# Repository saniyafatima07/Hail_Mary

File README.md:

# Low Cost Precision Guidance and Smart Electronic Fuze System for a 155 mm Artillery Shell

A low cost Precision Guidance System Kit prototype designed as a modular electronics package that can be integrated with an existing 155 mm artillery shell form factor. The system combines inertial sensing, GNSS positioning, environmental monitoring, BLDC based actuation and multi mode event detection to demonstrate the architecture of a retrofit guidance and electronic fuze platform.

## Demo Video

https://github.com/user-attachments/assets/ea4bcfed-2732-404f-be3d-91d5685b1a28

## Overview

The **Low Cost Precision Guidance and Smart Electronic Fuze System** is focused on integrating embedded sensing, navigation, actuation and a multi-mode electronic fuze architecture.

The system is designed around a modular embedded platform that combines inertial sensing, GNSS positioning, atmospheric monitoring, power telemetry, proximity detection, impact/event sensing, and **BLDC based actuation**.

The current V1 prototype uses an **ESP32** as the primary embedded controller and integrates:

- **MPU6050**:  6 axis inertial measurement
- **NEO-6M**:  GNSS positioning
- **BMP280**:  Barometric pressure and temperature
- **INA219**:  Voltage and current monitoring
- **IR Proximity Sensor**:  Proximity detection
- **SW-240**:  Impact/vibration event detection
- **BLDC Motor**:  Actuation mechanism for the prototype guidance subsystem

The system supports a **Multi-Mode Smart Fuze architecture** consisting of:

- **Proximity Mode**
- **Time Mode**
- **Impact Mode**

The V1 platform is intended primarily for **Testing, sensor integration, firmware development, simulation, telemetry, and proof of concept validation**.

---

## Project Objectives

The project aims to develop a compact and modular embedded platform capable of supporting:

1. Inertial sensing
2. GNSS positioning
3. Environmental sensing
4. Power monitoring
5. Proximity detection
6. Impact/event detection
7. BLDC-based actuation
8. Multi mode fuze state management
9. Sensor fusion
10. Real time telemetry

---

## Prototype Hardware

| Component | Function | Interface |
|---|---|---|
| **ESP32** | Main microcontroller | — |
| **MPU6050** | 6 axis inertial measurement | I2C |
| **NEO-6M** | GNSS/GPS positioning | UART |
| **BMP280** | Barometric pressure and temperature | I2C |
| **INA219** | Voltage and current monitoring | I2C |
| **IR Sensor** | Proximity detection | GPIO |
| **SW-240** | Impact/vibration detection | GPIO |
| **BLDC Motor** | Prototype actuation | Motor Driver / PWM |

---

## Simulation Stack                                                                                                                                                                      
                                                                                                                                                                                            
   The simulation is a three-layer chain, from pure physics to the real embedded                                                                                                            
   controller. Each layer validates the one above it, and every equation is                                                                                                                 
   traceable to published exterior-ballistics literature (McCoy *Modern Exterior                                                                                                            
   Ballistics*, Raza & Wang 2022, Cheng 2019, Chusilp 2012, Glebocki 2022).                                                                                                                 
                                                                                                                                                                                            
   ```text                                                                                                                                                                                  
   +---------------------------------------------------------------+                                                                                                                        
   |  LAYER 1 — 3-DOF FLIGHT PHYSICS (truth model)                 |                                                                                                                        
   |  point-mass trajectory: ISA atmosphere, Mach-dependent Cd,    |                                                                                                                        
   |  altitude wind profile, spin decay, Magnus, yaw of repose     |                                                                                                                        
   +------------------------------+--------------------------------+                                                                                                                        
                                  |                                                                                                                                                         
           +----------------------+----------------------+                                                                                                                                  
           v                                             v                                                                                                                                  
   +---------------------------+   +--------------------------------------+                                                                                                                 
   | LAYER 2 — HARDWARE-IN-    |   | LAYER 3 — ONBOARD-GNC SIL            |                                                                                                                 
   | THE-LOOP (HIL)            |   | (guidance_ordnance.m)                |                                                                                                                 
   | (guided_sensor.m)         |   | firmware_true.ino's exact math       |                                                                                                                 
   | PC flies the physics,     |   | (estimator + impact predictor +      |                                                                                                                 
   | REAL ESP32 streams real   |   | guidance law) flies the round using  |                                                                                                                 
   | sensor telemetry over     |   | ONLY noisy simulated baro/GPS at     |                                                                                                                 
   | UART; PC streams back     |   | board rates. Validates the onboard   |                                                                                                                 
   | canard commands in        |   | algorithm BEFORE flashing.           |                                                                                                                 
   | real time (1x - 4x).      |   |                                      |                                                                                                                 
   +---------------------------+   +--------------------------------------+                                                                                                                 
 ```

The GNC Math (implemented in firmware + validated in sim)                                                                                                                                  
                                                                                                                                                                                            
 - Firing solution (Chusilp 2012): bisection on gun elevation, secant                                                                                                                       
   iteration on azimuth for wind-drift cancellation.                                                                                                                                        
 - State estimation on board: baro altitude via hypsometric equation;                                                                                                                       
   vertical speed from a first-order complementary filter                                                                                                                                   
   vz ← 0.8·vz + 0.2·(Δh/Δt) at 10 Hz; GPS velocity smoothing at 1 Hz.                                                                                                                      
 - Impact Point Prediction (IPP) (McCoy; Raza & Wang 2022 use MPLT — we use                                                                                                                 
   the analytic point-mass equivalent an ESP32 can run in µs):                                                                                                                              
   closed-form time-to-impact τ = (vz + √(vz² + 2gz))/g, then drag-decay                                                                                                                    
   ballistic coast x_imp = x + vx·(1 − e^(−kd·τ))/kd.                                                                                                                                       
 - Guidance law: saturated proportional correction                                                                                                                                          
   δ = sat(Kp·(x_tgt − x_imp), ±15°), active post-apogee, 1 Hz.                                                                                                                             
 - Single-channel roll-orientation steering (Cheng 2019, Raza & Wang 2022):                                                                                                                 
   fixed-cant canards on the fuze cone; force orientation is the control                                                                                                                    
   variable, matching the dual-spin PGK architecture (M1156, Burke & Pergolizzi 2008).

## System Architecture

```text
                         +-------------------------+
                         |          ESP32          |
                         |    Main Controller      |
                         +------------+------------+
                                      |
              +-----------------------+-----------------------+
              |                       |                       |
              v                       v                       v
        +-----------+           +-----------+           +-----------+
        |    I2C    |           |   UART    |           |   GPIO    |
        |    Bus    |           | Interface |           |  Inputs   |
        +-----+-----+           +-----+-----+           +-----+-----+
              |                       |                       |
       +------+------+------+          |                 +----+----+
       |      |      |      |          |                 |         |
       v      v      v      |          v                 v         v
    MPU6050 BMP280 INA219  |       NEO-6M           IR Sensor   SW-240
       |      |      |      |          |             Proximity   Impact
       +------+------+------+          |                 |         |
              |                         |                 |         |
              v                         v                 |         |
       Motion / Environment       GNSS Position           |         |
              |                         |                 |         |
              +-------------+-----------+-----------------+---------+
                            |
                            v
                  +----------------------+
                  |   Sensor Processing  |
                  |   & State Estimation |
                  +----------+-----------+
                             |
                +------------+------------+
                |                         |
                v                         v
        +---------------+         +---------------+
        | Guidance &    |         | Smart Fuze    |
        | Navigation    |         | Manager       |
        +-------+-------+         +-------+-------+
                |                         |
                v                         |
        +---------------+                 |
        | Actuation     |                 |
        | Controller    |                 |
        +-------+-------+                 |
                |                         |
                v                         |
        +---------------+                 |
        | BLDC Motor &  |                 |
        | Motor Driver  |                 |
        +---------------+                 |
                                          |
                              +-----------+-----------+
                              |           |           |
                              v           v           v
                         +---------+ +---------+ +---------+
                         |Proximity| |  Time   | | Impact  |
                         |  Mode   | |  Mode   | |  Mode   |
                         +---------+ +---------+ +---------+
                              |           |           |
                              +-----------+-----------+
                                          |
                                          v
                                +----------------------+
                                | Telemetry & System   |
                                | Status Monitoring    |
                                +----------------------+

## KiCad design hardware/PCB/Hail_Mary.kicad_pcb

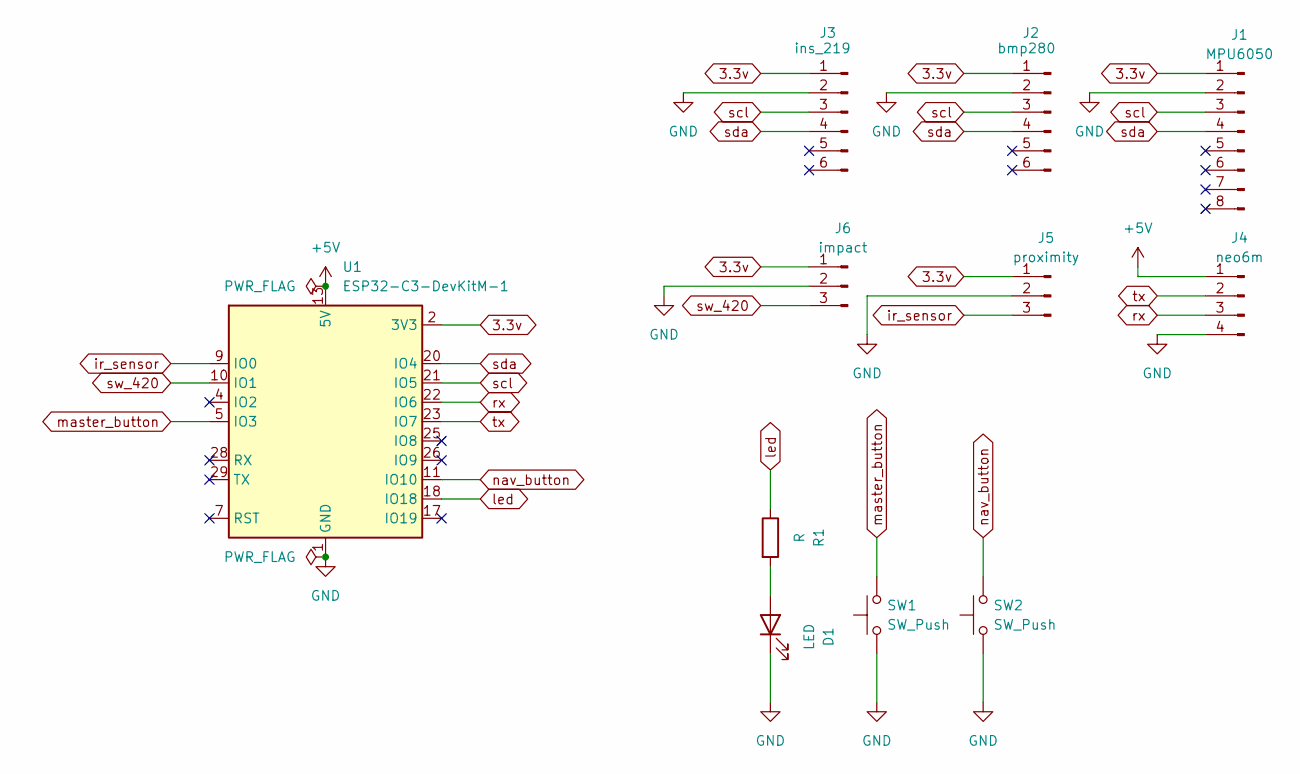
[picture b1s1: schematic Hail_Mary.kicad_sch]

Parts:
D1: LED; LED_D5.0mm
J1: MPU6050; PinHeader_1x08_P1.00mm_Vertical
J2: bmp280; PinHeader_1x06_P1.00mm_Vertical
J3: ins_219; PinHeader_1x06_P1.00mm_Vertical
J4: neo6m; PinHeader_1x04_P1.00mm_Vertical
J5: proximity; PinHeader_1x03_P1.00mm_Vertical
J6: impact; PinHeader_1x03_P1.00mm_Vertical
R1: R; R_Axial_DIN0207_L6.3mm_D2.5mm_P10.16mm_Horizontal
SW1, SW2: SW_Push; SW_PUSH_6mm_H4.3mm
U1: ESP32-C3-DevKitM-1

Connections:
3.3v: J1.1, J2.1, J3.1, J5.1, J6.1, U1.2 (3V3), U1.3 (3V3)
+5V: J4.1, U1.13 (5V), U1.14 (5V)
GND: D1.1 (K), J1.2, J2.2, J3.2, J4.4, J5.2, J6.2, SW1.1, SW2.1, U1.1 (GND), U1.6 (GND), U1.8 (GND), U1.12 (GND), U1.15 (GND), U1.16 (GND), U1.19 (GND), U1.24 (GND), U1.27 (GND), U1.30 (GND)
unnamed: D1.2 (A), R1.2
ir_sensor: J5.3, U1.9 (IO0)
led: R1.1, U1.18 (IO18)
master_button: SW1.2, U1.5 (IO3)
nav_button: SW2.2, U1.11 (IO10)
rx: J4.3, U1.22 (IO6)
scl: J1.3, J2.3, J3.3, U1.21 (IO5)
sda: J1.4, J2.4, J3.4, U1.20 (IO4)
sw_420: J6.3, U1.10 (IO1)
tx: J4.2, U1.23 (IO7)

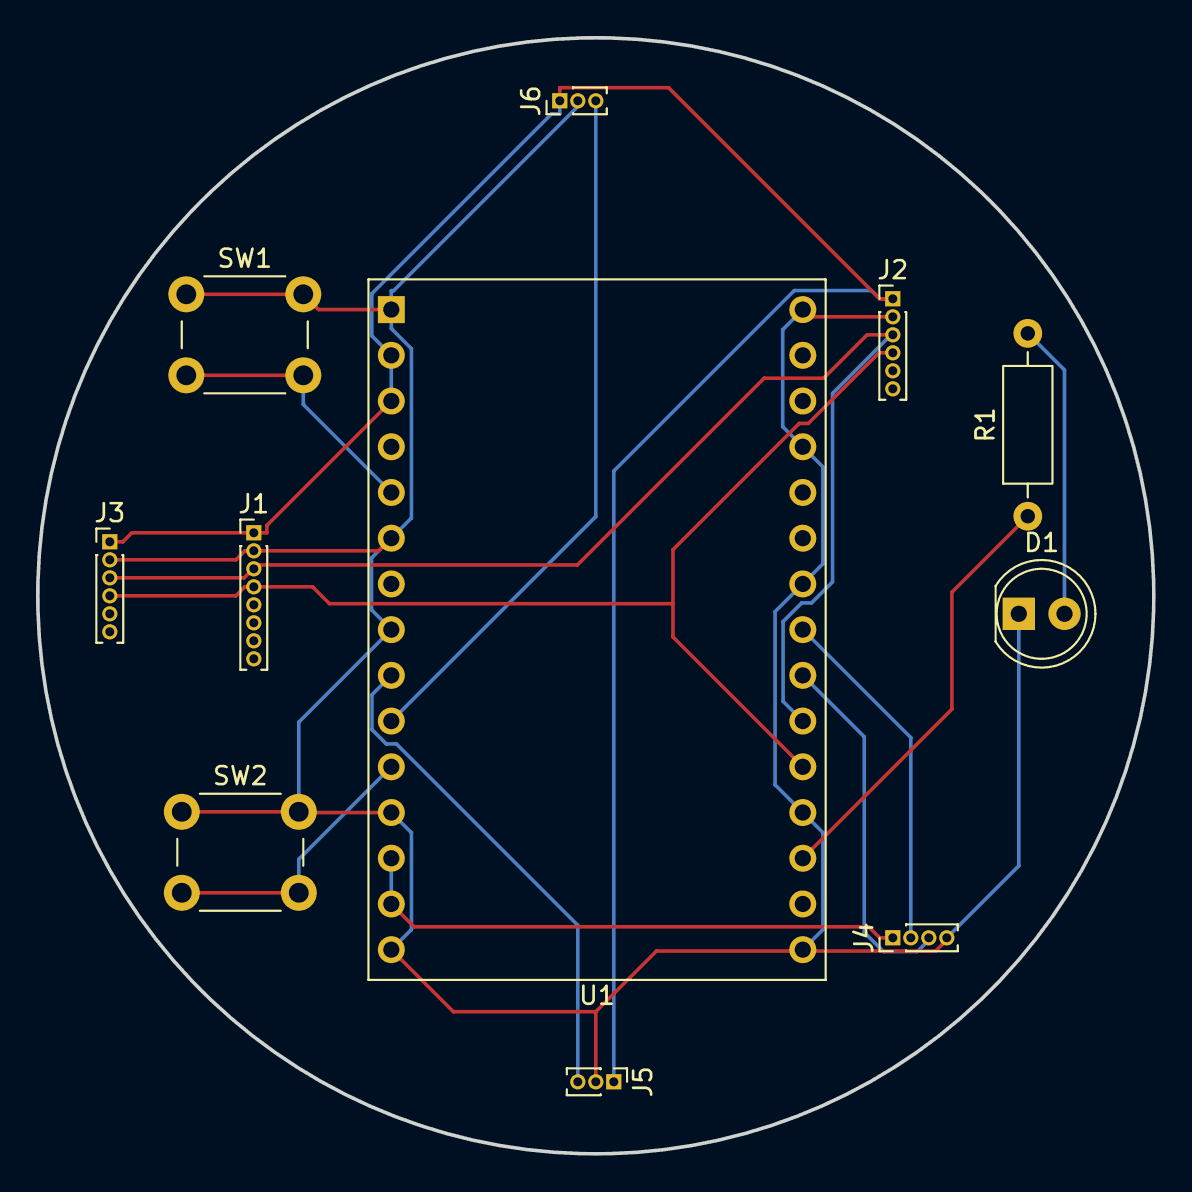
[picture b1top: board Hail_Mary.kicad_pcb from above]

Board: 2 copper layers, 62.0 x 62.0 mm, 11 parts (0 on the bottom side), 13 nets.
